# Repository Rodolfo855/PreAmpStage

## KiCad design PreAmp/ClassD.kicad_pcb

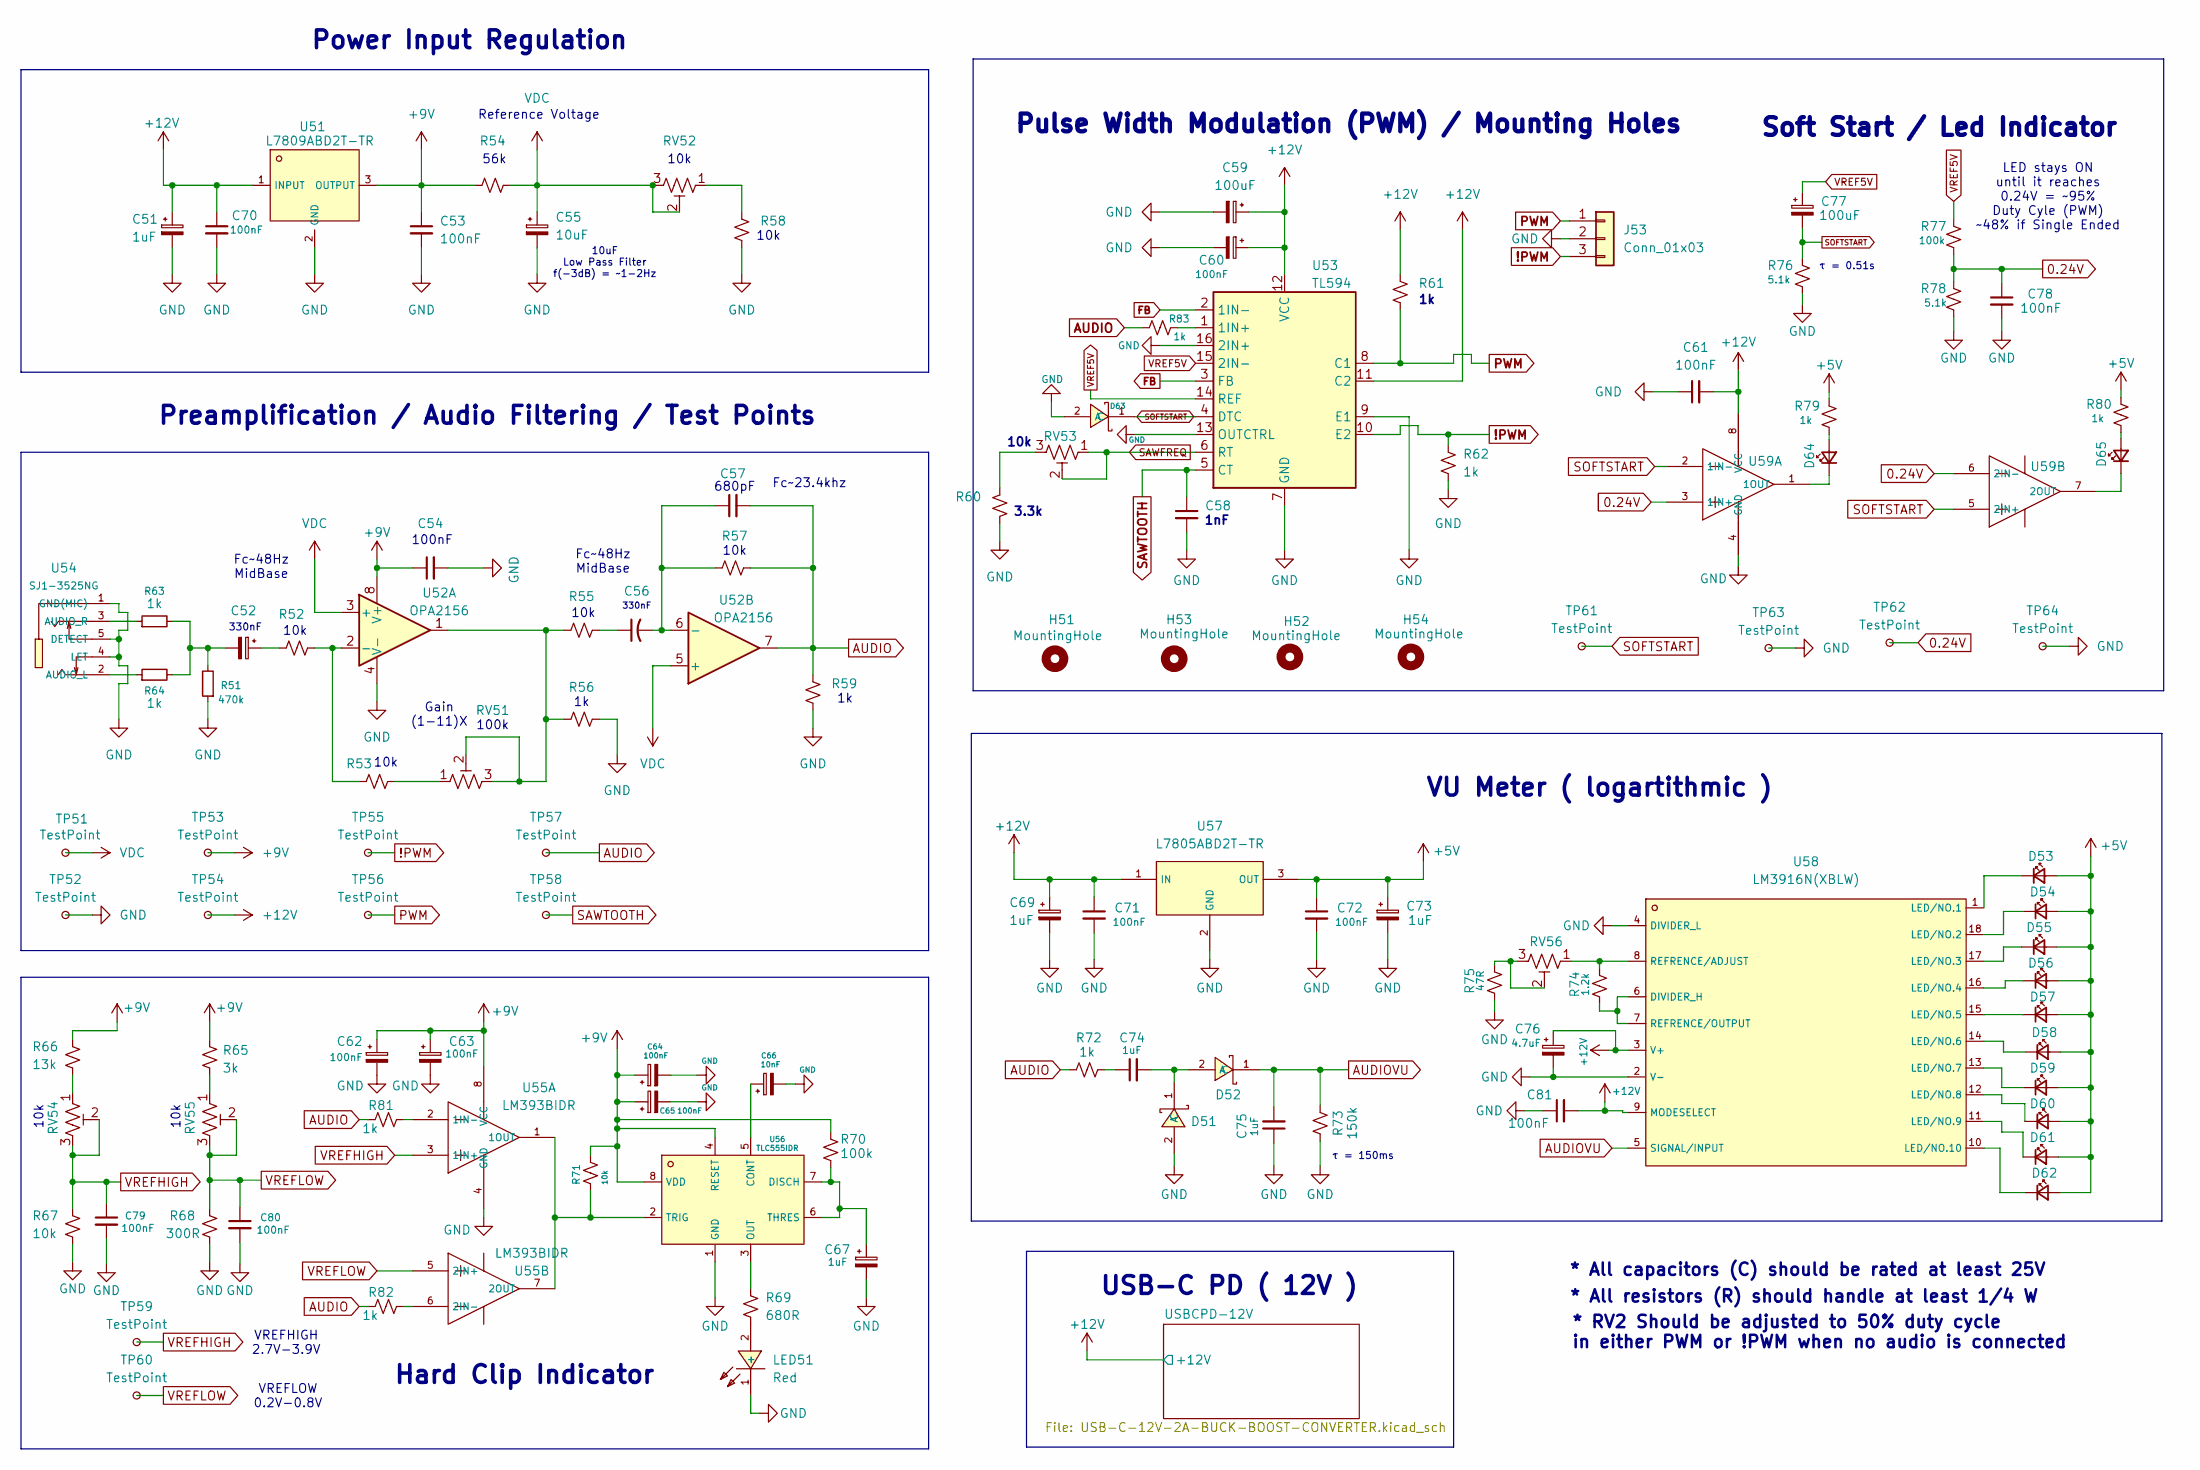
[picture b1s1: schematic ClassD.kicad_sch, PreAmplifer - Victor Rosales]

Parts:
C51, C52, C56, C67, C69, C73, C74, C75: 1uF; C_0805_2012Metric
C53, C54, C60, C61, C62, C63, C64, C65, C70, C71, C72, C78, C79, C80, C81: 100nF; C_0805_2012Metric
C55: 10uF; C_0805_2012Metric
C57: 680pF; C_0805_2012Metric
C58: 1nF; C_0805_2012Metric
C59, C77: 100uF; CP_Radial_D6.3mm_P2.50mm
C66: 10nF; C_0805_2012Metric
C76: 4.7uF; C_0805_2012Metric
D51, D52, D63: 1N5819_C437199; C437199_SMA_L4_4-W2_6-LS5_0-RD; LCSC C437199
D53, D54, D55, D56, D57, D58, D65: Green; LED_0805_2012Metric
D59, D60: Orange; LED_0805_2012Metric
D61, D62: Red; LED_0805_2012Metric
D64: Amber/Yellow; LED_0805_2012Metric
H51, H52, H53, H54: MountingHole; MountingHole_2.2mm_M2_Pad_Via
J53: Conn_01x03; JST_XH_B3B-XH-A_1x03_P2.50mm_Vertical
LED51: Red; C84256_LED0805-RD; LCSC C84256
R51: 470k; R_0805_2012Metric
R52, R53, R55, R57, R58, R67, R71: 10k; R_0805_2012Metric
R54: 56k; R_0805_2012Metric
R56, R59, R61, R62, R63, R64, R72, R79, R80, R81, R82, R83: 1k; R_0805_2012Metric
R60: 3.3k; R_0805_2012Metric
R65: 3k; R_0805_2012Metric
R66: 13k; R_0805_2012Metric
R68: 300R; R_0805_2012Metric
R69: 680R; R_0805_2012Metric
R70, R77: 100k; R_0805_2012Metric
R73: 150k; R_0805_2012Metric
R74: 1.2k; R_0805_2012Metric
R75: 47R; R_0805_2012Metric
R76, R78: 5.1k; R_0805_2012Metric
RV51: 100k; Potentiometer_Bourns_3296W_Vertical
RV52, RV53, RV54, RV55: 10k; Potentiometer_Bourns_3296W_Vertical
RV56: 1k; Potentiometer_Bourns_3296W_Vertical
TP51, TP52, TP53, TP54, TP55, TP56, TP57, TP58, TP59, TP60, TP61, TP62, TP63, TP64: TestPoint; C5277086_TEST-TH_BD2_54-P1_4_RED
U51: L7809ABD2T-TR; C262905_D2PAK_L10_0-W9_0-P2_54-LS15_0-BR; LCSC C262905
U52: OPA2156; C1850241_SOIC-8_L5_0-W4_0-P1_27-LS6_0-BL
U53: TL594; C157346_SOIC-16_L9_9-W3_9-P1_27-LS6_0-BL
U54: SJ1-3525NG; C4991936_AUDIO-TH_SJ1-3525NG; LCSC C4991936
U55, U59: LM393BIDR; C2865059_SOIC-8_L4_9-W3_9-P1_27-LS6_0-BL; LCSC C2865059
U56: TLC555IDR; C6987_SOIC-8_L4_9-W3_9-P1_27-LS6_0-BL; LCSC C6987
U57: L7805ABD2T-TR; C86206_TO-263-2_L10_0-W9_2-P5_08-LS15_3-TL-CW; LCSC C86206
U58: LM3916N(XBLW); C55109575_PDIP-18_L22_9-W6_4-P2_54-LS7_9-BL; LCSC C55109575

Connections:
0.24V: C78.1, R77.2, R78.1, TP62.1, U59.3 (1IN+), U59.6 (2IN-)
!PWM: J53.3, R62.1, TP55.1, U53.10 (E2)
+5V: C72.1, C73.1, D53.2 (A), D54.2 (A), D55.2 (A), D56.2 (A), D57.2 (A), D58.2 (A), D59.2 (A), D60.2 (A), D61.2 (A), D62.2 (A), R79.1, R80.1, U57.3 (OUT)
+9V: C53.1, C54.1, C62.1, C63.1, C64.1, C65.1, R54.1, R65.1, R66.1, R70.1, R71.1, TP53.1, U51.3 (OUTPUT), U52.8 (V+), U55.8 (VCC), U56.4 (RESET), U56.8 (VDD)
+12V: C51.1, C59.1, C60.1, C61.2, C69.1, C70.1, C71.1, C76.1, C81.2, R61.1, TP54.1, U51.1 (INPUT), U53.11 (C2), U53.12 (VCC), U57.1 (IN), U58.3 (V+), U58.9 (MODESELECT), U59.8 (VCC); also elsewhere on the board
AUDIO: C57.2, R57.2, R59.1, R72.1, R81.1, R82.1, R83.1, TP57.1, U52.7
AUDIOVU: C75.2, D52.1 (C), R73.1, U58.5 (SIGNAL/INPUT)
FB: U53.2 (1IN-), U53.3 (FB)
GND: C51.2, C53.2, C54.2, C55.2, C58.2, C59.2, C60.2, C61.1, C62.2, C63.2, C64.2, C65.2, C66.2, C67.2, C69.2, C70.2, C71.2, C72.2, C73.2, C75.1, C76.2, C78.2, C79.2, C80.2, C81.1, D51.2 (A), D63.2 (A), J53.2, LED51.1 (-), R51.1, R56.2, R58.2, R59.2, R60.2, R62.2, R67.2, R68.2, R73.2, R75.2, R76.2, R78.2, TP52.1, TP63.1, TP64.1, U51.2 (GND), U52.4 (V-), U53.7 (GND), U53.9 (E1), U53.13 (OUTCTRL), U53.16 (2IN+), U54.1 (GND(MIC)), U54.4 (LET), U54.5 (DETECT), U55.4 (GND), U56.1 (GND), U57.2 (GND), U58.2 (V-), U58.4 (DIVIDER_L), U59.4 (GND); also elsewhere on the board
unnamed: C52.1, R52.1
unnamed: C52.2, R51.2, R63.2, R64.2
unnamed: C56.1, R55.2
unnamed: C74.1, R72.2
unnamed: C74.2, D51.1 (C), D52.2 (A)
unnamed: D53.1 (K), U58.1 (LED/NO.1)
unnamed: D54.1 (K), U58.18 (LED/NO.2)
unnamed: D55.1 (K), U58.17 (LED/NO.3)
unnamed: D56.1 (K), U58.16 (LED/NO.4)
unnamed: D57.1 (K), U58.15 (LED/NO.5)
unnamed: D58.1 (K), U58.14 (LED/NO.6)
unnamed: D59.1 (K), U58.13 (LED/NO.7)
unnamed: D60.1 (K), U58.12 (LED/NO.8)
unnamed: D61.1 (K), U58.11 (LED/NO.9)
unnamed: D62.1 (K), U58.10 (LED/NO.10)
unnamed: D64.2 (A), R79.2
unnamed: D64.1 (K), U59.1 (1OUT)
unnamed: D65.2 (A), R80.2
unnamed: D65.1 (K), U59.7 (2OUT)
unnamed: LED51.2 (+), R69.2
unnamed: R53.2, RV51.1
unnamed: R55.1, R56.1, RV51.2, RV51.3, U52.1
unnamed: R58.1, RV52.1
unnamed: R60.1, RV53.3
unnamed: R65.2, RV55.1
unnamed: R66.2, RV54.1
unnamed: R75.1, RV56.2, RV56.3
unnamed: R52.2, R53.1, U52.2 (-)
unnamed: C56.2, C57.1, R57.1, U52.6 (-)
unnamed: R83.2, U53.1 (1IN+)
unnamed: R64.1, U54.2 (AUDIO_L)
unnamed: R63.1, U54.3 (AUDIO_R)
unnamed: R81.2, U55.2 (1IN-)
unnamed: R71.2, U55.1 (1OUT), U55.7 (2OUT), U56.2 (TRIG)
unnamed: R82.2, U55.6 (2IN-)
unnamed: C66.1, U56.5 (CONT)
unnamed: C67.1, R70.2, U56.6 (THRES), U56.7 (DISCH)
unnamed: R69.1, U56.3 (OUT)
unnamed: R74.2, U58.6 (DIVIDER_H), U58.7 (REFRENCE/OUTPUT)
unnamed: R74.1, RV56.1, U58.8 (REFRENCE/ADJUST)
PWM: J53.1, R61.2, TP56.1, U53.8 (C1)
SAWFREQ: RV53.1, RV53.2, U53.6 (RT)
SAWTOOTH: C58.1, TP58.1, U53.5 (CT)
SOFTSTART: C77.2, D63.1 (C), R76.1, TP61.1, U53.4 (DTC), U59.2 (1IN-), U59.5 (2IN+)
VDC: C55.1, R54.2, RV52.2, RV52.3, TP51.1, U52.3 (+), U52.5 (+)
VREF5V: C77.1, R77.1, U53.14 (REF), U53.15 (2IN-)
VREFHIGH: C79.1, R67.1, RV54.2, RV54.3, TP59.1, U55.3 (1IN+)
VREFLOW: C80.1, R68.1, RV55.2, RV55.3, TP60.1, U55.5 (2IN+)

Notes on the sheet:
Pulse Width Modulation (PWM) / Mounting Holes
3.3k
Power Input Regulation
LED stays ON until it reaches 0.24V = ~95% Duty Cyle (PWM) ~48% if Single Ended
1nF
* All capacitors (C) should be rated at least 25V
100k
Soft Start / Led Indicator
Fc~23.4khz
Reference Voltage
330nF
10k
10uF Low Pass Filter f(-3dB) = ~1-2Hz
VU Meter ( logartithmic )
VREFLOW 0.2V-0.8V
τ = 150ms
* All resistors (R) should handle at least 1/4 W
τ = 0.51s
56k
680pF
VREFHIGH 2.7V-3.9V
USB-C PD ( 12V )
* RV2 Should be adjusted to 50% duty cycle in either PWM or !PWM when no audio is connected
Fc~48Hz MidBase
Preamplification / Audio Filtering / Test Points
Hard Clip Indicator
Gain (1-11)X
100nF

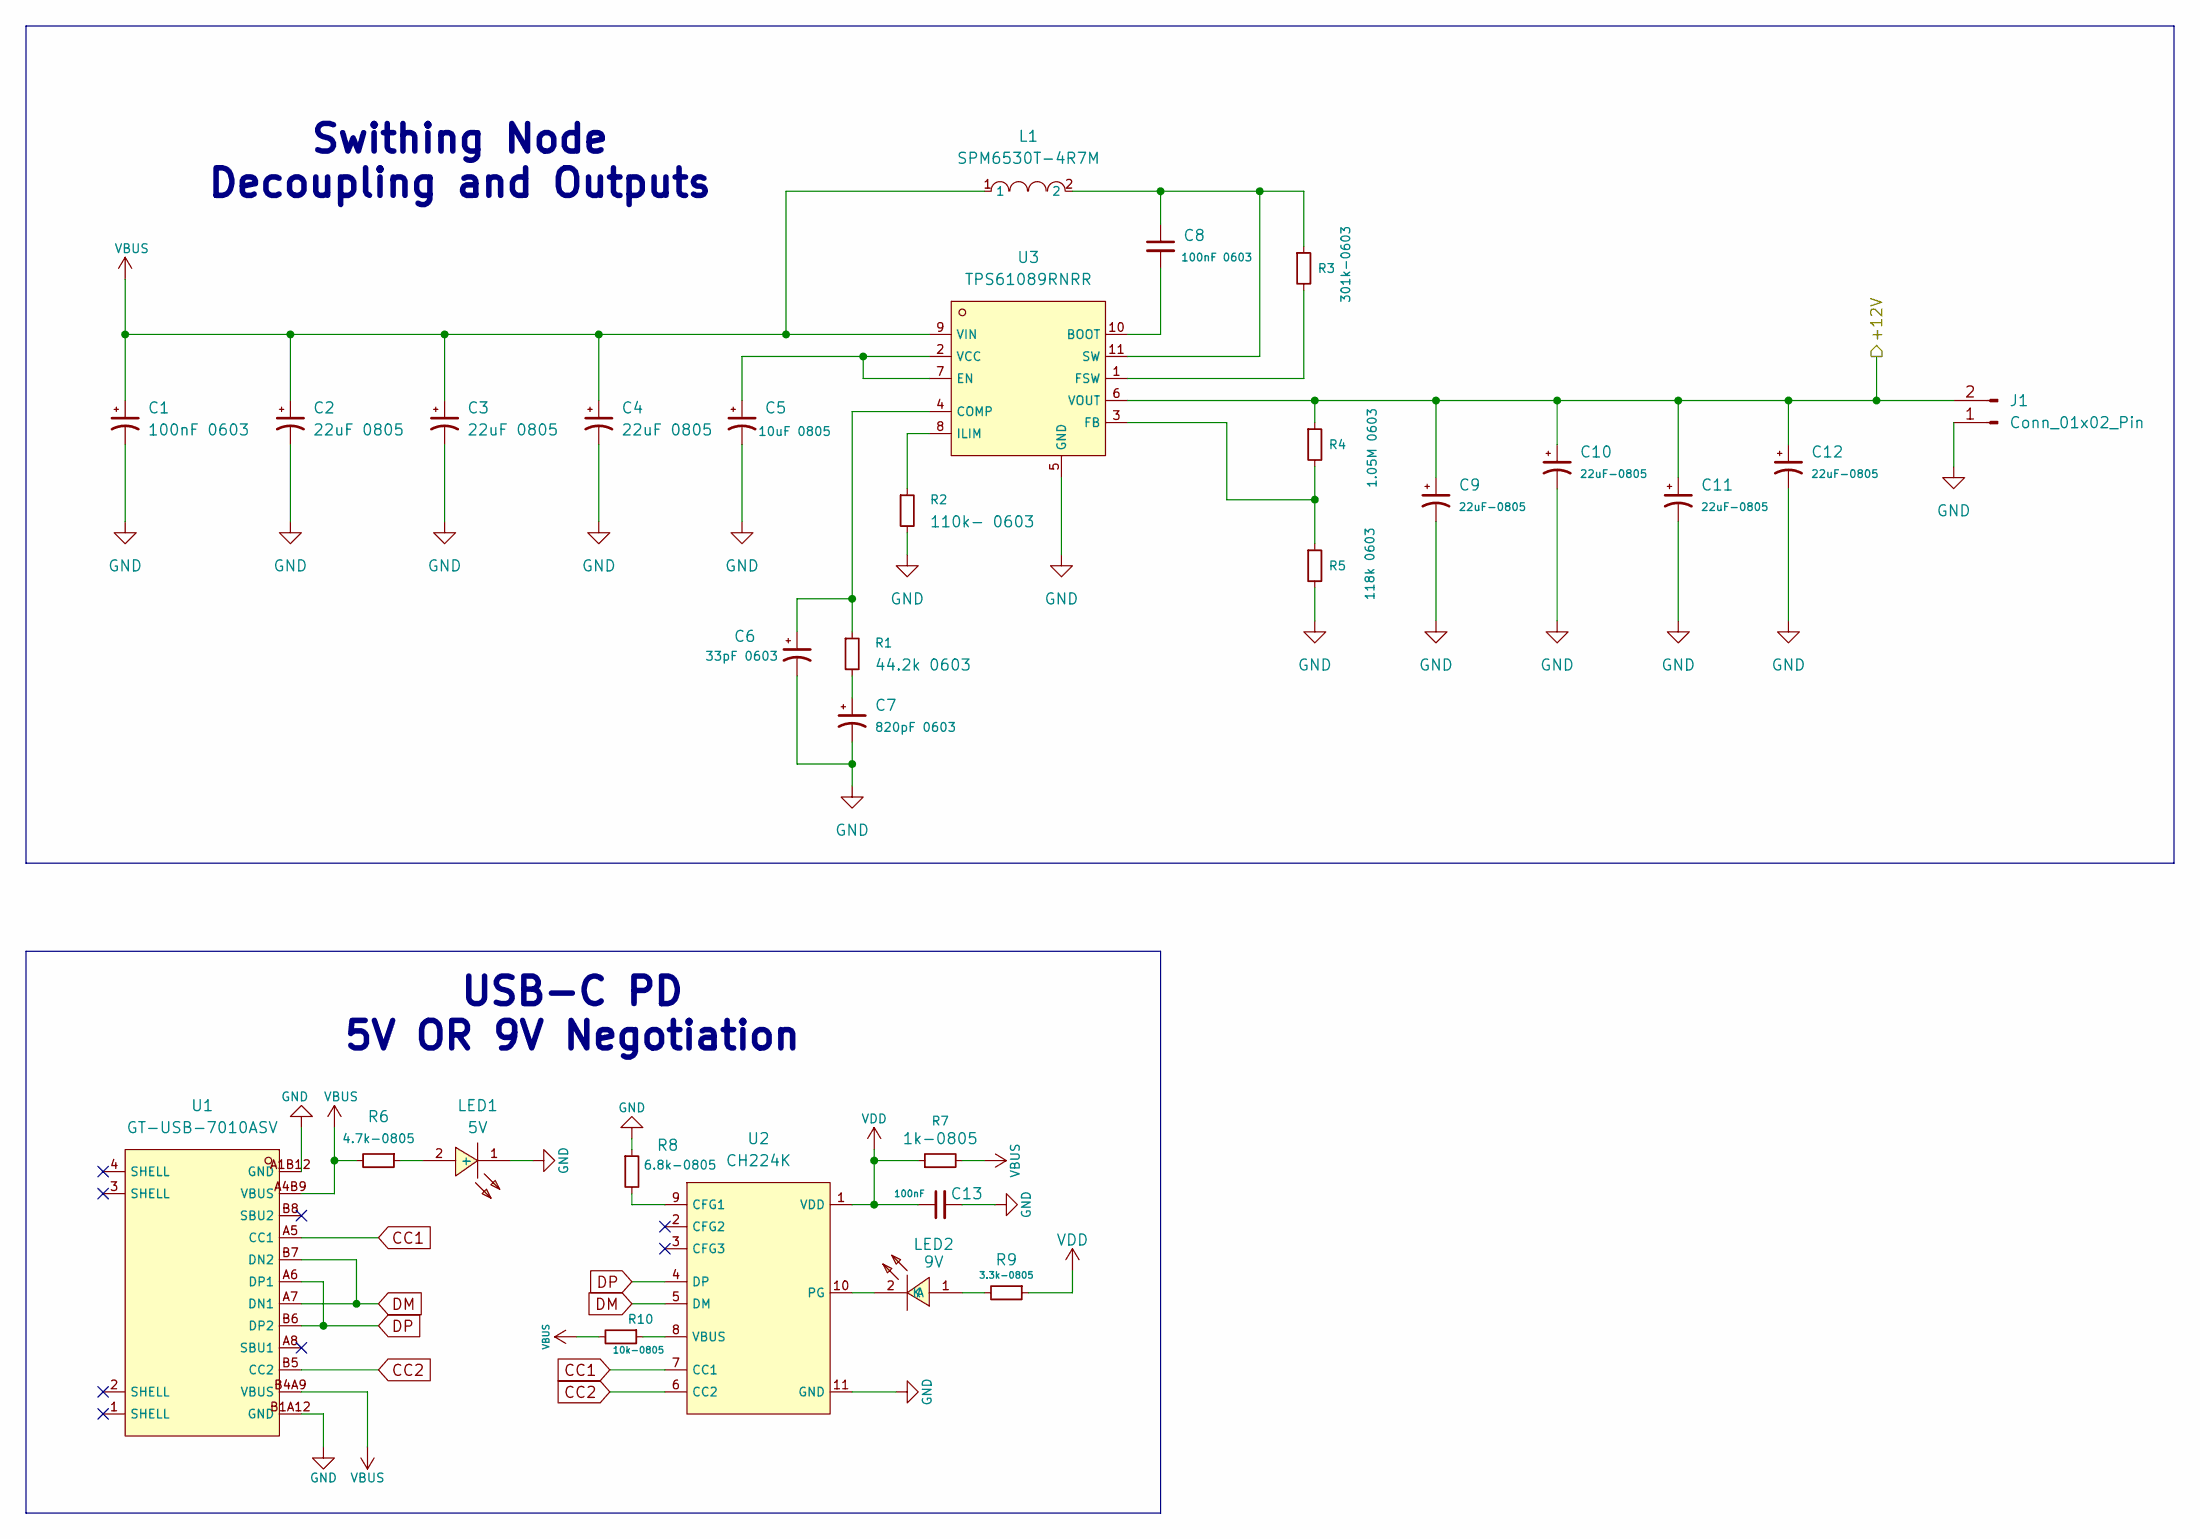
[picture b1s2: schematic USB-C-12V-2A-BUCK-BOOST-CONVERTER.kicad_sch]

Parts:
C1, C8: 100nF 0603; C_0603_1608Metric; LCSC C1591
C2, C3, C4: 22uF 0805; C_0805_2012Metric; LCSC C45783
C5: 10uF 0805; C_0805_2012Metric; LCSC C15850
C6: 33pF 0603; C_0603_1608Metric; LCSC C1663
C7: 820pF 0603; C_0603_1608Metric; LCSC C107057
C9, C10, C11, C12: 22uF-0805; C_0805_2012Metric; LCSC C45783
C13: 100nF; C_0603_1608Metric
J1: Conn_01x02_Pin; JST_XH_B2B-XH-A_1x02_P2.50mm_Vertical
L1: SPM6530T-4R7M; C76857_IND-SMD_L7_1-W6_5; LCSC C76857
LED1: 5V; C84256_LED0805-RD; LCSC C84256
LED2: 9V; C2297_LED0805-R-RD; LCSC C2297
R1: 44.2k 0603; R_0603_1608Metric; LCSC C23172
R2: 110k- 0603; R_0603_1608Metric; LCSC C25805
R3: 301k-0603; R_0603_1608Metric; LCSC C23024
R4: 1.05M 0603; R_0603_1608Metric; LCSC C22935
R5: 118k 0603; R_0603_1608Metric; LCSC C25805
R6: 4.7k-0805; R_0805_2012Metric
R7: 1k-0805; R_0805_2012Metric
R8: 6.8k-0805; R_0805_2012Metric
R9: 3.3k-0805; R_0805_2012Metric
R10: 10k-0805; R_0805_2012Metric
U1: GT-USB-7010ASV; C2988369_USB-C-SMD_G-SWITCH_GT-USB-7010ASV; LCSC C2988369
U2: CH224K; C970725_ESSOP-10_L4_9-W3_9-P1_0-LS6_0-TL-EP; LCSC C970725
U3: TPS61089RNRR; C165129_VQFN-HR_L2_5-W2_0-P0_50-TL-EP; LCSC C165129

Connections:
+12V: C9.1, C10.1, C11.1, C12.1, J1.2, R4.1, U3.6 (VOUT); also elsewhere on the board
CC1: U1.A5 (CC1), U2.7 (CC1)
CC2: U1.B5 (CC2), U2.6 (CC2)
DM: U1.A7 (DN1), U1.B7 (DN2), U2.5 (DM)
DP: U1.A6 (DP1), U1.B6 (DP2), U2.4 (DP)
GND: C1.2, C2.2, C3.2, C4.2, C5.2, C6.2, C7.2, C9.2, C10.2, C11.2, C12.2, C13.2, J1.1, LED1.1 (-), R2.2, R5.2, R8.1, U1.A1B12 (GND), U1.B1A12 (GND), U2.11 (GND), U3.5 (GND); also elsewhere on the board
unnamed: C7.1, R1.2
unnamed: LED1.2 (+), R6.1
unnamed: LED2.1 (A), R9.2
unnamed: LED2.2 (K), U2.10 (PG)
unnamed: R8.2, U2.9 (CFG1)
unnamed: R10.1, U2.8 (VBUS)
unnamed: C8.2, U3.10 (BOOT)
unnamed: C6.1, R1.1, U3.4 (COMP)
unnamed: C5.1, U3.2 (VCC), U3.7 (EN)
unnamed: R4.2, R5.1, U3.3 (FB)
unnamed: R3.2, U3.1 (FSW)
unnamed: R2.1, U3.8 (ILIM)
unnamed: C8.1, L1.2, R3.1, U3.11 (SW)
VBUS: C1.1, C2.1, C3.1, C4.1, L1.1, R6.2, R7.2, R10.2, U1.A4B9 (VBUS), U1.B4A9 (VBUS), U3.9 (VIN)
VDD: C13.1, R7.1, R9.1, U2.1 (VDD)

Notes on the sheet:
Swithing Node Decoupling and Outputs
USB-C PD 5V OR 9V Negotiation

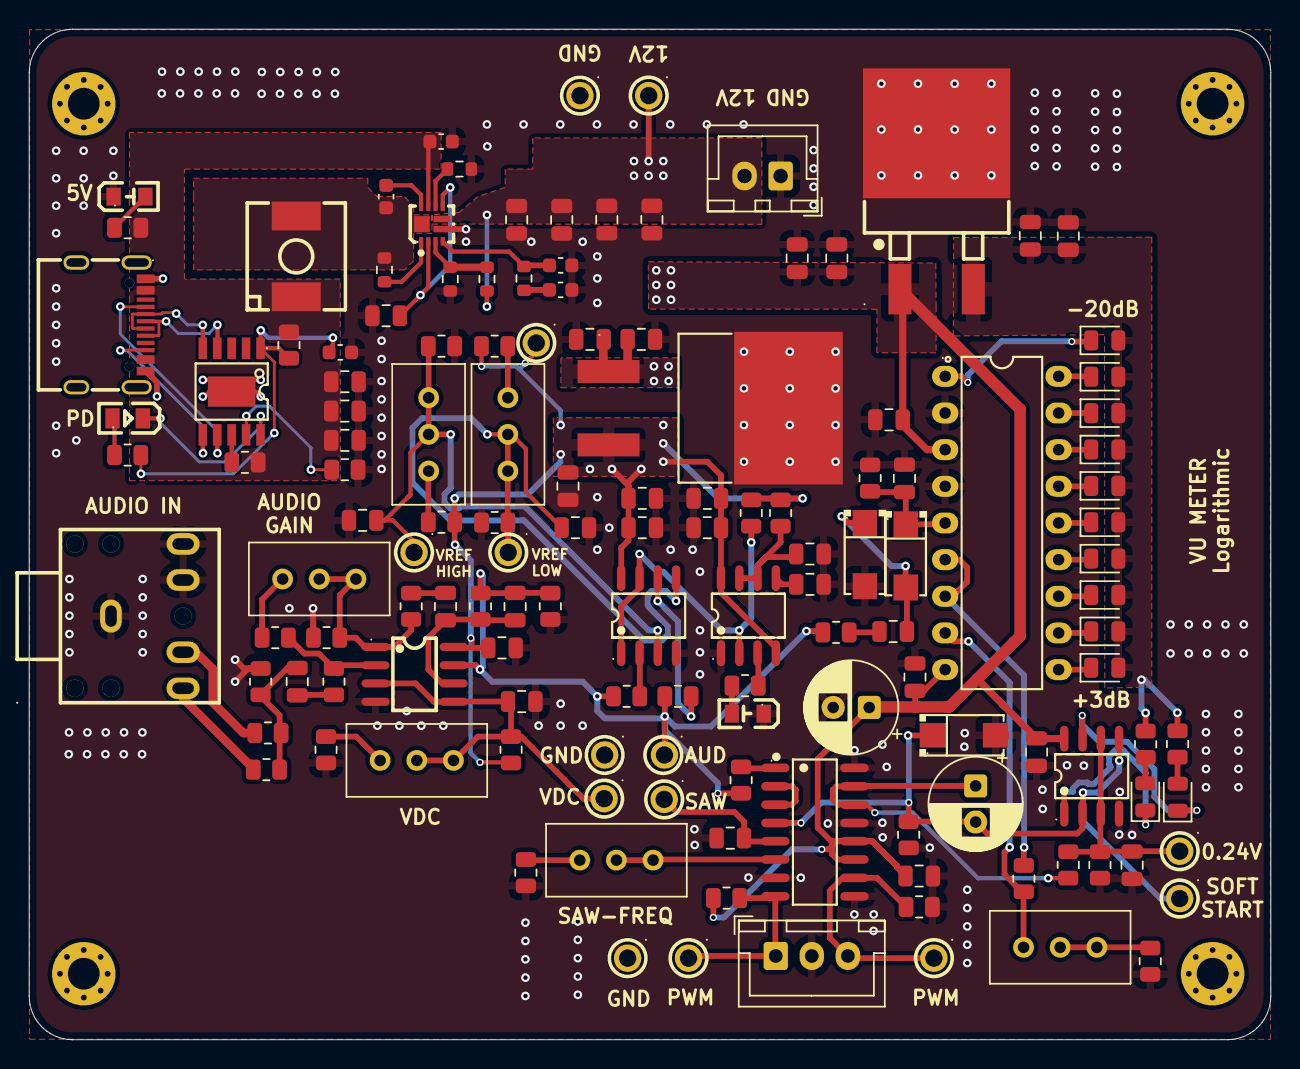
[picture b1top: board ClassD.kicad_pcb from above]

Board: 2 copper layers, 86.0 x 70.0 mm, 143 parts (0 on the bottom side), 76 nets.
